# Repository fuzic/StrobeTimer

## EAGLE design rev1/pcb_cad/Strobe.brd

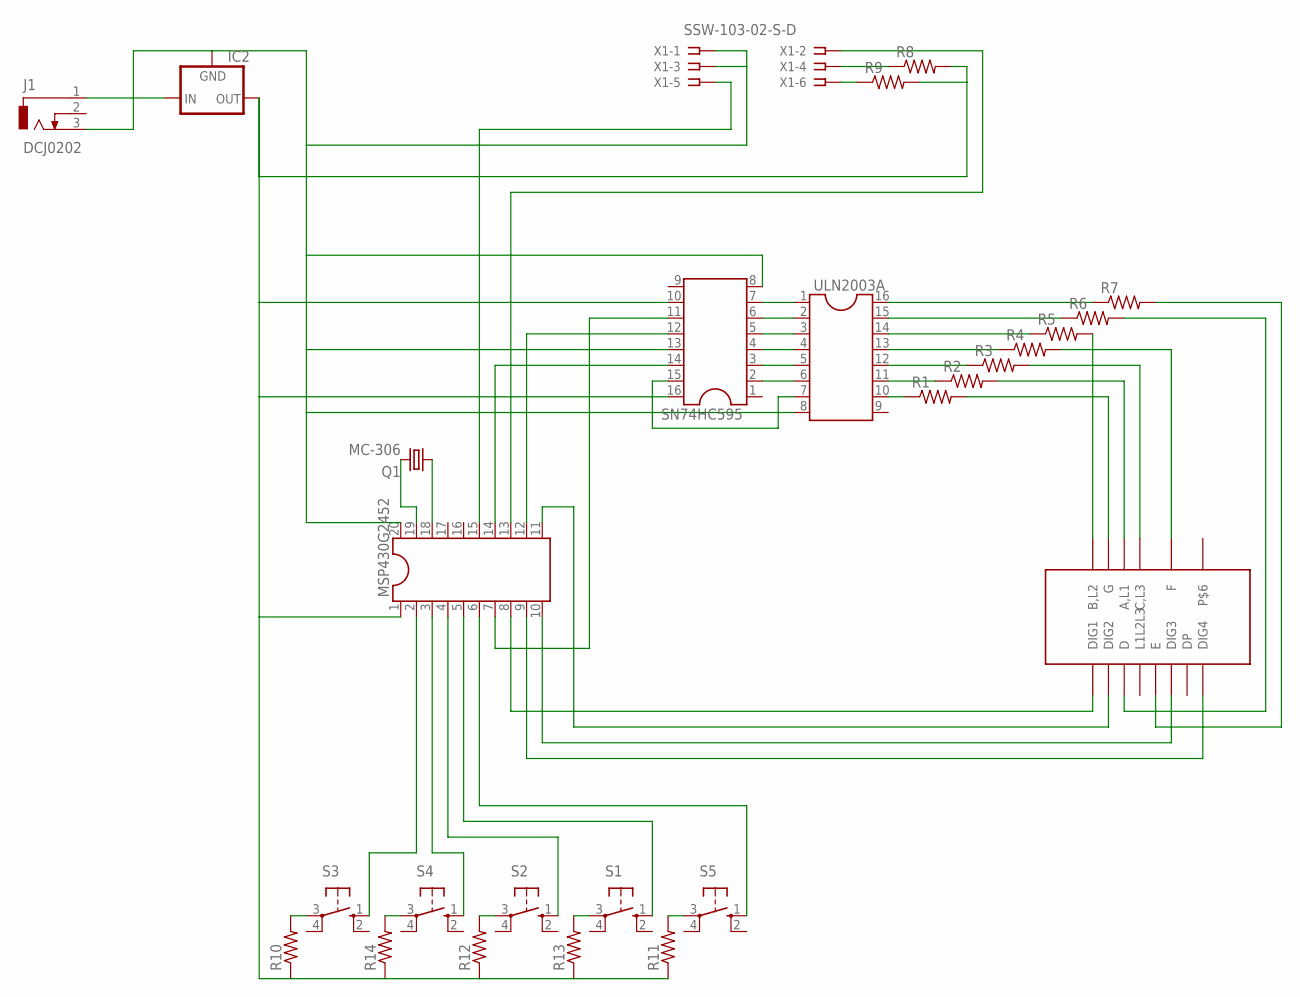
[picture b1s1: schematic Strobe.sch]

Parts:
IC2: 78XXS
J1: DCJ0202
LTC-4627JS: SEG4X7; HDSP-R
MSP430G2452: DIL20S; SOCKET-20
Q1: MC-306
R1, R2, R3, R4, R5, R6, R7, R8, R9, R10, R11, R12, R13, R14: R-US_0207/7; 0207/7
S1, S2, S3, S4, S5: 10-XX; B3F-10XX
SN74HC595: DIL16
ULN2003A: DIL16
X1: SSW-103-02-S-D

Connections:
unnamed: MSP430G2452.19, Q1.4 (2)
unnamed: MSP430G2452.14, SN74HC595.14
unnamed: MSP430G2452.7, SN74HC595.11
unnamed: LTC-4627JS.DIG4, MSP430G2452.9
unnamed: MSP430G2452.2, S3.1 (S)
unnamed: LTC-4627JS.DIG1, MSP430G2452.8
unnamed: LTC-4627JS.DIG2, MSP430G2452.11
unnamed: IC2.IN, J1.1
unnamed: MSP430G2452.12, SN74HC595.12
unnamed: SN74HC595.6, ULN2003A.2
unnamed: MSP430G2452.6, S5.1 (S)
unnamed: MSP430G2452.5, S1.1 (S)
unnamed: MSP430G2452.4, S2.1 (S)
unnamed: MSP430G2452.3, S4.1 (S)
unnamed: R7.1, ULN2003A.16
unnamed: R6.1, ULN2003A.15
unnamed: R5.1, ULN2003A.14
unnamed: R4.1, ULN2003A.13
unnamed: R3.1, ULN2003A.12
unnamed: R2.1, ULN2003A.11
unnamed: R1.1, ULN2003A.10
unnamed: SN74HC595.7, ULN2003A.1
unnamed: SN74HC595.5, ULN2003A.3
unnamed: SN74HC595.4, ULN2003A.4
unnamed: SN74HC595.3, ULN2003A.5
unnamed: SN74HC595.2, ULN2003A.6
unnamed: SN74HC595.15, ULN2003A.7
unnamed: LTC-4627JS.G, R1.2
unnamed: LTC-4627JS.A,L1, R2.2
unnamed: LTC-4627JS.C,L3, R3.2
unnamed: LTC-4627JS.F, R4.2
unnamed: LTC-4627JS.B,L2, R5.2
unnamed: LTC-4627JS.D, R6.2
unnamed: LTC-4627JS.E, R7.2
unnamed: MSP430G2452.15, X1.5
unnamed: R12.2, S2.3
unnamed: R14.2, S4.3
unnamed: R13.2, S1.3
unnamed: R11.2, S5.3
unnamed: R10.2, S3.3
unnamed: IC2.OUT, MSP430G2452.1, R8.2, R9.2, R10.1, R11.1, R12.1, R13.1, R14.1, SN74HC595.10, SN74HC595.16
unnamed: IC2.GND, J1.3, MSP430G2452.20, SN74HC595.8, SN74HC595.13, ULN2003A.8, X1.1, X1.3
unnamed: MSP430G2452.18, Q1.1
unnamed: R9.1, X1.6
unnamed: R8.1, X1.4
unnamed: MSP430G2452.13, X1.2
unnamed: LTC-4627JS.DIG3, MSP430G2452.10

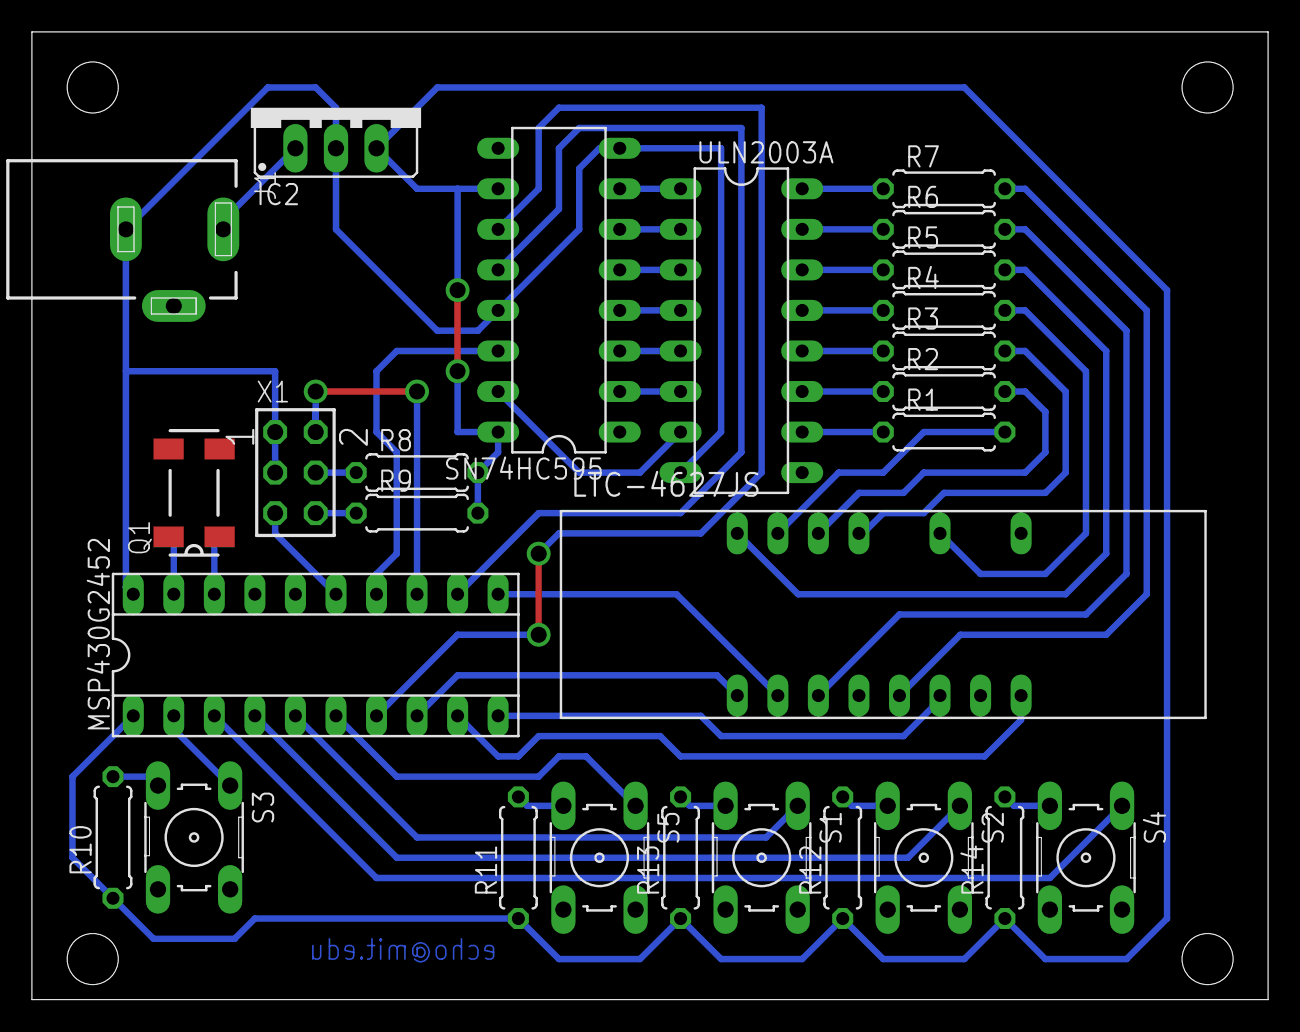
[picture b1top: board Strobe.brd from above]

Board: 2 copper layers, 77.5 x 60.6 mm, 27 parts (0 on the bottom side), 47 nets.
